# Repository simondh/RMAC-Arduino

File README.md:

# RMAC-Arduino
Remote Monitoring And Control

Old, obsolete Arduino C++ code.
Delete eventually?

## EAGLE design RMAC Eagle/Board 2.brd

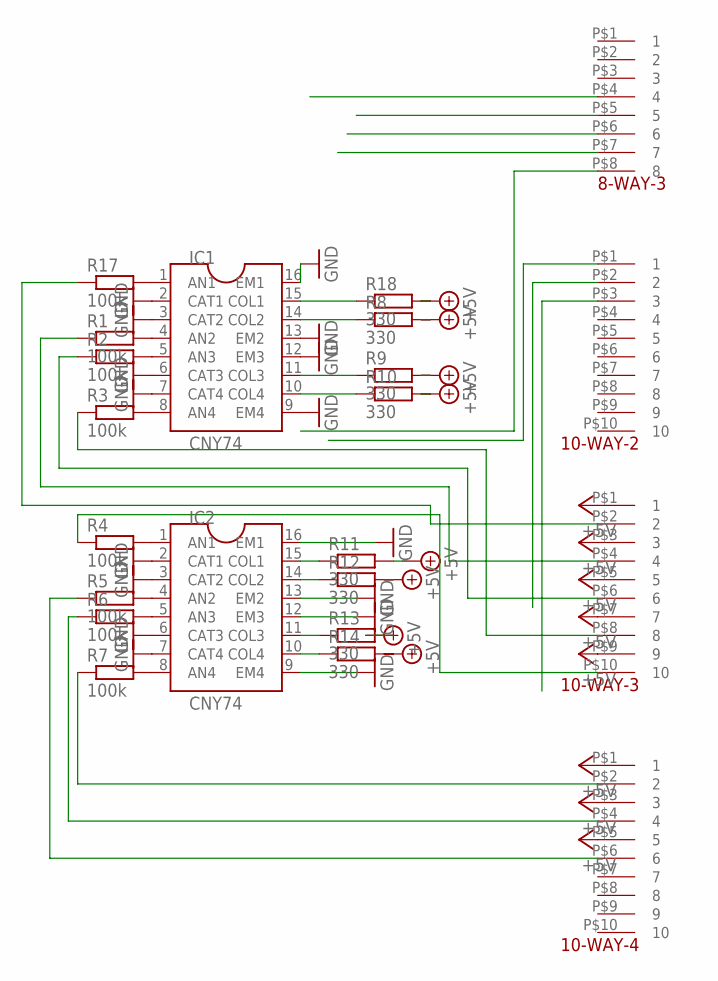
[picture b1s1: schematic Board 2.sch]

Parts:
8-WAY-3: SDH8PIN
10-WAY-2, 10-WAY-3, 10-WAY-4: SDH10PIN
IC1, IC2: IC-CNY74-16DIL
R1, R2, R3, R4, R5, R6, R7, R17: 100k; P0613V
R8, R9, R10, R11, R12, R13, R14, R18: 330; P0613V

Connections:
+5V: 10-WAY-3.P$1 (1), 10-WAY-3.P$3 (3), 10-WAY-3.P$5 (5), 10-WAY-3.P$7 (7), 10-WAY-3.P$9 (9), 10-WAY-4.P$1 (1), 10-WAY-4.P$3 (3), 10-WAY-4.P$5 (5), R8.2, R9.2, R10.2, R11.2, R12.2, R13.2, R18.2
GND: IC1.2 (CAT1), IC1.3 (CAT2), IC1.6 (CAT3), IC1.7 (CAT4), IC1.9 (EM4), IC1.12 (EM3), IC1.13 (EM2), IC1.16 (EM1), IC2.2 (CAT1), IC2.3 (CAT2), IC2.6 (CAT3), IC2.7 (CAT4), IC2.9 (EM4), IC2.12 (EM3), IC2.13 (EM2), IC2.16 (EM1)
unnamed: IC1.1 (AN1), R17.2
unnamed: IC1.4 (AN2), R1.2
unnamed: IC1.5 (AN3), R2.2
unnamed: IC1.8 (AN4), R3.2
unnamed: IC2.1 (AN1), R4.2
unnamed: IC2.4 (AN2), R5.2
unnamed: IC2.5 (AN3), R6.2
unnamed: IC2.8 (AN4), R7.2
unnamed: 10-WAY-3.P$8 (8), R3.1
unnamed: 10-WAY-3.P$6 (6), R2.1
unnamed: 10-WAY-3.P$4 (4), R1.1
unnamed: 10-WAY-3.P$2 (2), R17.1
unnamed: 10-WAY-3.P$10 (10), R4.1
unnamed: 10-WAY-4.P$2 (2), R7.1
unnamed: 10-WAY-4.P$4 (4), R6.1
unnamed: 10-WAY-4.P$6 (6), R5.1
unnamed: IC1.14 (COL2), R8.1
unnamed: IC1.11 (COL3), R9.1
unnamed: IC1.10 (COL4), R10.1
unnamed: IC1.15 (COL1), R18.1
unnamed: IC2.14 (COL2), R12.1
unnamed: IC2.15 (COL1), R11.1
unnamed: IC2.11 (COL3), R13.1
unnamed: IC2.10 (COL4), R14.1

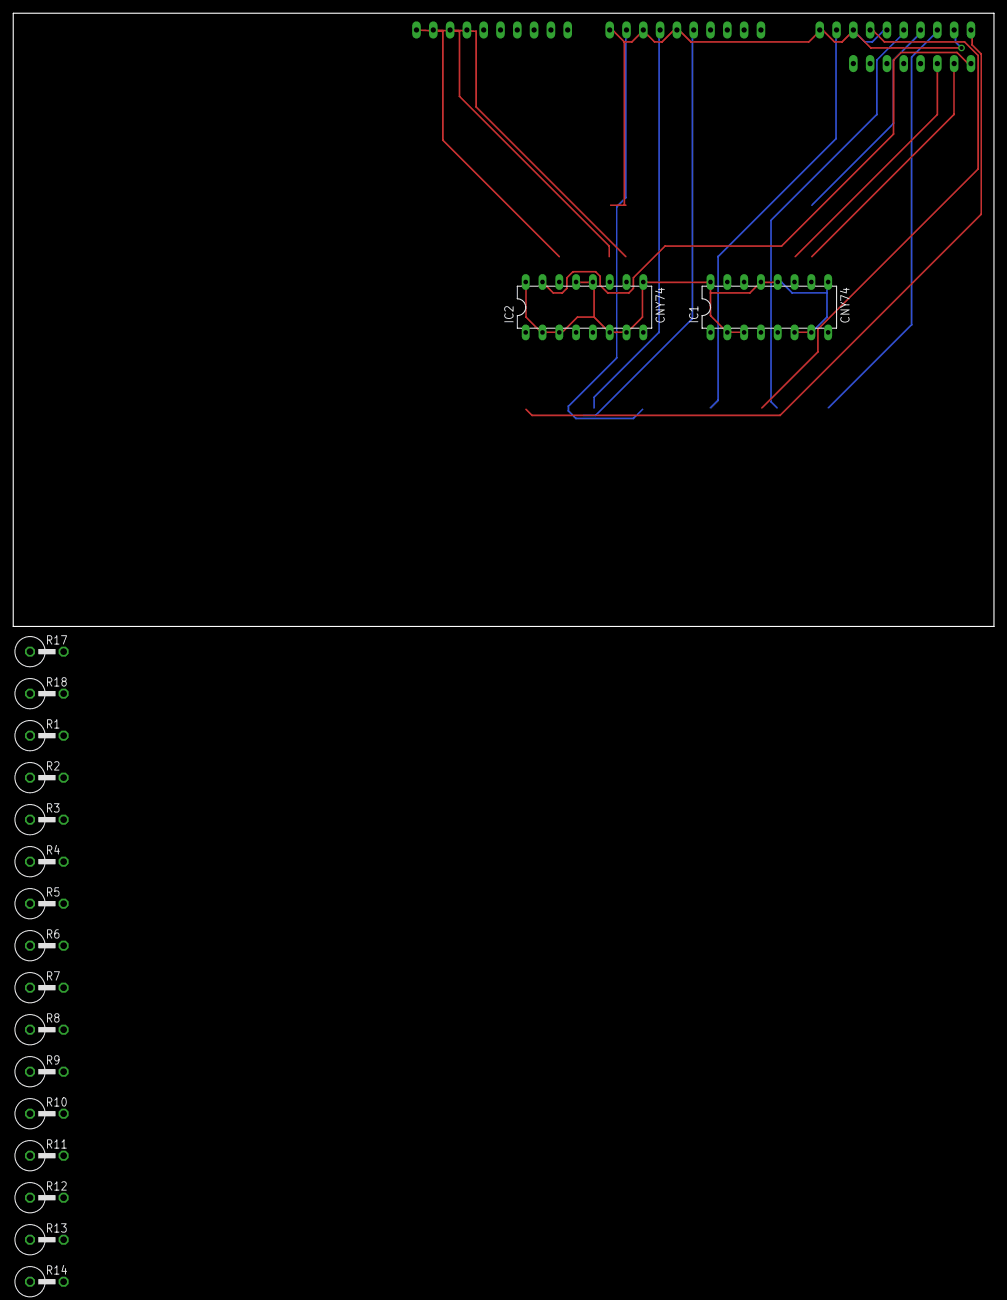
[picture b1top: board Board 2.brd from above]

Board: 2 copper layers, 148.3 x 92.7 mm, 22 parts (0 on the bottom side), 26 nets.

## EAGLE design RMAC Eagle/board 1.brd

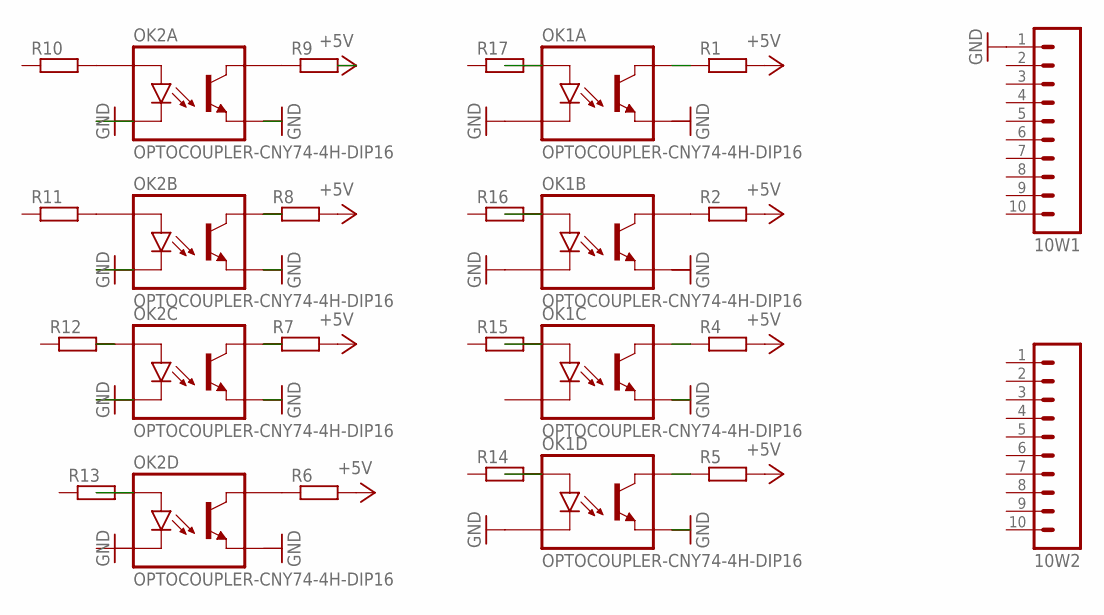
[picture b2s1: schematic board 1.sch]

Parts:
10W1, 10W2: M10; 10P
OK1, OK2: OPTOCOUPLER-CNY74-4H-DIP16; DIL16-3
R1, R2, R4, R5, R6, R7, R8, R9, R10, R11, R12, R13, R14, R15, R16, R17: R-EU_0207/7; 0207/7

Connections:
+5V: R1.2, R2.2, R4.2, R5.2, R6.2, R7.2, R8.2, R9.2
ALM3: OK1.4 (A1), R16.2
ALM4: OK1.1 (A1), R17.2
GND: 10W1.1, OK1.2 (C1), OK1.3 (C1), OK1.7 (C1), OK1.10 (EMITTER1), OK1.12 (EMITTER1), OK2.2 (C1), OK2.3 (C1), OK2.6 (C1), OK2.12 (EMITTER1), OK2.13 (EMITTER1), OK2.16 (EMITTER1)
unnamed: OK1.15 (COLLECTOR1), R1.1
unnamed: OK2.14 (COLLECTOR1), R8.1
unnamed: OK1.11 (COLLECTOR1), R4.1
unnamed: OK1.9 (COLLECTOR1), R5.1
unnamed: OK2.9 (COLLECTOR1), R6.1
unnamed: OK2.4 (A1), R11.2
unnamed: OK2.5 (A1), R12.2
unnamed: OK2.8 (A1), R13.2
unnamed: OK1.8 (A1), R14.2
unnamed: OK1.5 (A1), R15.2
unnamed: OK1.14 (COLLECTOR1), R2.1
unnamed: OK2.1 (A1), R10.2
unnamed: OK2.15 (COLLECTOR1), R9.1
unnamed: OK2.11 (COLLECTOR1), R7.1

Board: 2 copper layers, 20 parts (1 on the bottom side), 18 nets, no tracks yet.

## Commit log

2015-01-10 BaseCommit
    Read/write config files, Site class OK
2015-01-11 Classes site, digitalAlarm and authorised User complete, archive and restore complete, log management good - still needs delete old files.
2015-01-11 Added message Q, looks OK, needs more testing
2015-01-15 going well, just added check-alarm for digital
2015-01-17 Tidy up
2015-01-17 Added design and build docs to the repo
2015-01-17 Added layout & parts list (and .gitignore)
2015-04-07 just bringing to tidy state
2015-04-08 Deleted sync error file, update sync
